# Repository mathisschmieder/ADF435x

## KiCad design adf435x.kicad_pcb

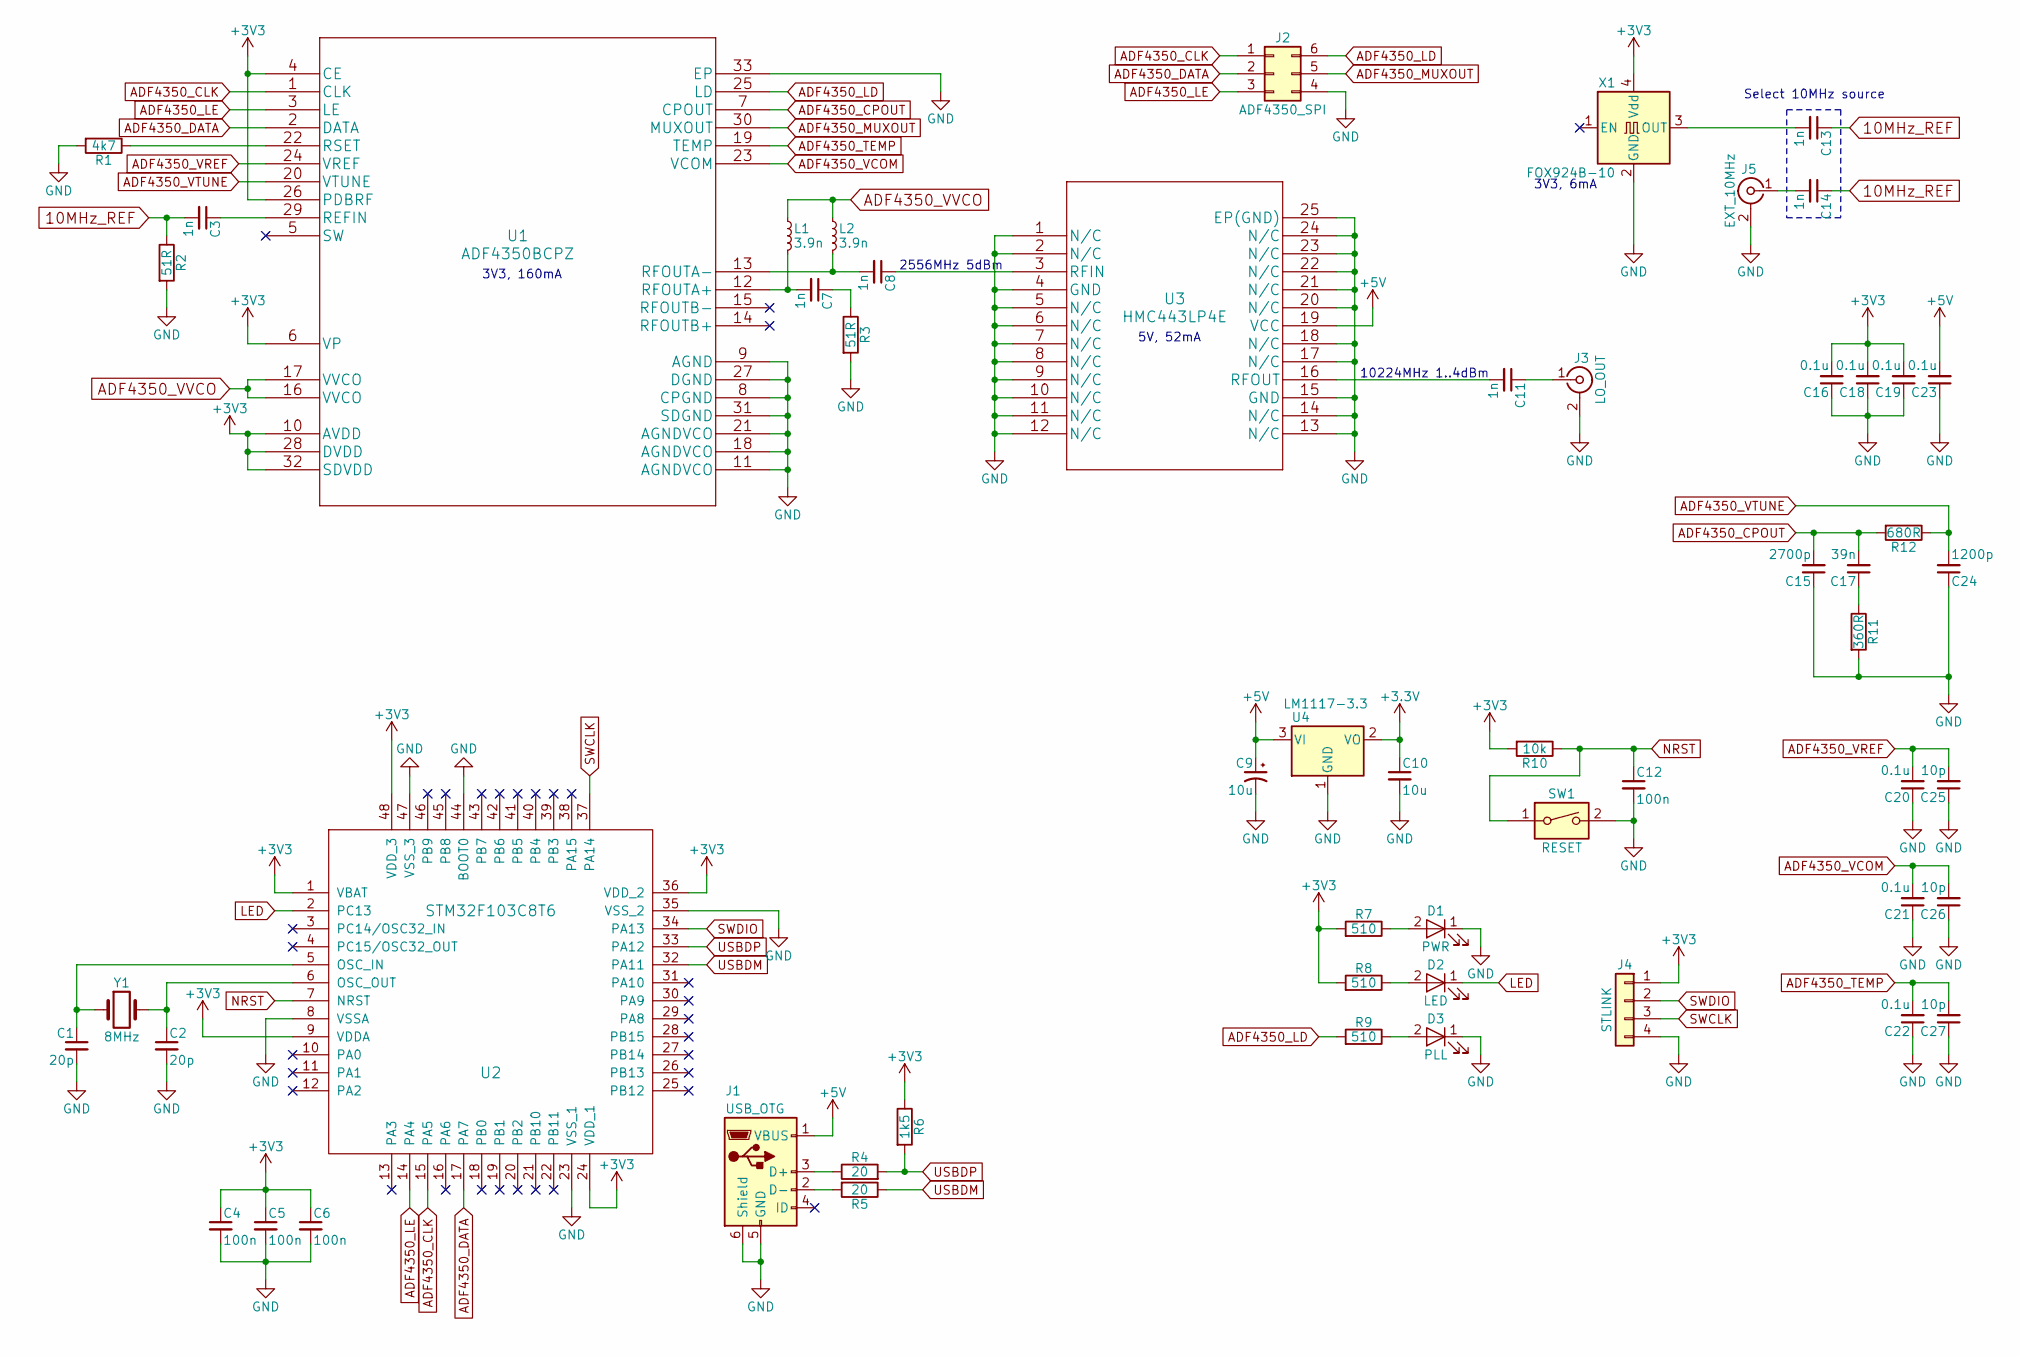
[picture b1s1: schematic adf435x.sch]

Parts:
C1, C2: 20p; C_0603
C3, C7, C8, C11, C13, C14: 1n; C_0603
C4, C5, C6, C12: 100n; C_0603
C9: 10u; CP_Tantalum_Case-A_EIA-3216-18_Reflow
C10: 10u; C_0603
C15: 2700p; C_0603
C16, C18, C19, C20, C21, C22, C23: 0.1u; C_0603
C17: 39n; C_0603
C24: 1200p; C_0603
C25, C26: 10p; C_0603
C27: 10p; LED_0603
D1: PWR; LED_0603
D2: LED; LED_0603
D3: PLL; LED_0603
J1: USB_OTG; USB_Micro-B_Wuerth-629105150521
J2: ADF4350_SPI; Pin_Header_Straight_2x03_Pitch1.27mm_SMD
J3: LO_OUT; Molex_SMA_Jack_Edge_Mount
J4: STLINK; Pin_Header_Straight_1x04_Pitch2.54mm
J5: EXT_10MHz; SMA_SMD_Jack_Straight
L1, L2: 3.9n; L_0603
R1: 4k7; R_0603
R2, R3: 51R; R_0603
R4, R5: 20; R_0603
R6: 1k5; R_0603
R7, R8, R9: 510; R_0603
R10: 10k; R_0603
R11: 360R; R_0603
R12: 680R; R_0603
SW1: RESET; SW_SPST_B3U-1000P
U1: ADF4350BCPZ; ADF4350BCPZ-RL
U2: STM32F103C8T6; LQFP-48_7x7mm_Pitch0.5mm
U3: HMC443LP4E
U4: LM1117-3.3; SOT-223-3_TabPin2
X1: FOX924B-10; Oscillator_SMD_Abracon_ASE-4pin_3.2x2.5mm
Y1: 8MHz; Crystal_SMD_Abracon_ABM3-2pin_5.0x3.2mm

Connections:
10MHz_REF: C3.2, C13.1, C14.1, R2.1
+5V: C9.1, C23.2, J1.1 (VBUS), U3.19 (VCC), U4.3 (VI)
ADF4350_CLK: J2.1, U1.1 (CLK), U2.15 (PA5)
ADF4350_CPOUT: C15.2, C17.2, R12.2, U1.7 (CPOUT)
ADF4350_DATA: J2.2, U1.2 (DATA), U2.17 (PA7)
ADF4350_LD: J2.6, R9.2, U1.25 (LD)
ADF4350_LE: J2.3, U1.3 (LE), U2.14 (PA4)
ADF4350_MUXOUT: J2.5, U1.30 (MUXOUT)
ADF4350_TEMP: C22.2, C27.2, U1.19 (TEMP)
ADF4350_VCOM: C21.2, C26.2, U1.23 (VCOM)
ADF4350_VREF: C20.2, C25.2, U1.24 (VREF)
ADF4350_VTUNE: C24.2, R12.1, U1.20 (VTUNE)
ADF4350_VVCO: L1.1, L2.1, U1.16 (VVCO), U1.17 (VVCO)
GND: C1.2, C2.2, C4.2, C5.2, C6.2, C9.2, C10.2, C12.2, C15.1, C16.1, C18.1, C19.1, C20.1, C21.1, C22.1, C23.1, C24.1, C25.1, C26.1, C27.1, D1.1 (K), D3.1 (K), J1.5 (GND), J1.6 (Shield), J2.4, J3.2 (Ext), J4.4, J5.2 (Ext), R1.2, R2.2, R3.2, R11.2, SW1.2, U1.8 (CPGND), U1.9 (AGND), U1.11 (AGNDVCO), U1.18 (AGNDVCO), U1.21 (AGNDVCO), U1.27 (DGND), U1.31 (SDGND), U1.33 (EP), U2.8 (VSSA), U2.23 (VSS_1), U2.35 (VSS_2), U2.44 (BOOT0), U2.47 (VSS_3), U3.1 (N/C), U3.2 (N/C), U3.4 (GND), U3.5 (N/C), U3.6 (N/C), U3.7 (N/C), U3.8 (N/C), U3.9 (N/C), U3.10 (N/C), U3.11 (N/C), U3.12 (N/C), U3.13 (N/C), U3.14 (N/C), U3.15 (GND), U3.17 (N/C), U3.18 (N/C), U3.20 (N/C), U3.21 (N/C), U3.22 (N/C), U3.23 (N/C), U3.24 (N/C), U3.25 (EP(GND)), U4.1 (GND), X1.2 (GND); also elsewhere on the board
LED: D2.1 (K), U2.2 (PC13)
NRST: C12.1, R10.1, SW1.1, U2.7 (NRST); also elsewhere on the board
unnamed: C1.1, U2.5 (OSC_IN), Y1.1
unnamed: C2.1, U2.6 (OSC_OUT), Y1.2
unnamed: C3.1, U1.29 (REFIN)
unnamed: C7.1, R3.1
unnamed: C7.2, L1.2, U1.12 (RFOUTA+)
unnamed: C8.1, U3.3 (RFIN)
unnamed: C8.2, L2.2, U1.13 (RFOUTA-)
unnamed: C11.1, J3.1 (In)
unnamed: C11.2, U3.16 (RFOUT)
unnamed: C13.2, X1.3 (OUT)
unnamed: C14.2, J5.1 (In)
unnamed: C17.1, R11.1
unnamed: D1.2 (A), R7.1
unnamed: D2.2 (A), R8.1
unnamed: D3.2 (A), R9.1
unnamed: J1.2 (D-), R5.2
unnamed: J1.3 (D+), R4.1
unnamed: R1.1, U1.22 (RSET)
SWCLK: J4.3, U2.37 (PA14)
SWDIO: J4.2, U2.34 (PA13)
USBDM: R5.1, U2.32 (PA11)
USBDP: R4.2, R6.2, U2.33 (PA12)

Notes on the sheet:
2556MHz 5dBm
10224MHz 1..4dBm
Select 10MHz source
5V, 52mA
3V3, 6mA
3V3, 160mA

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
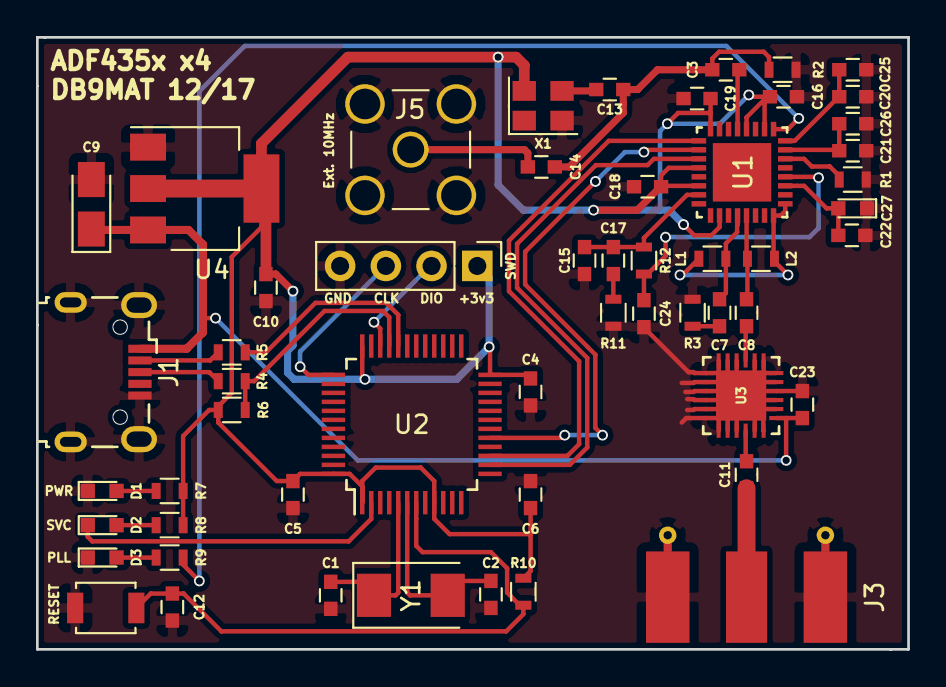
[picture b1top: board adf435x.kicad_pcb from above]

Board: 2 copper layers, 48.4 x 34.0 mm, 55 parts (0 on the bottom side), 38 nets.

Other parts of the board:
RESET: RESET; SW_SPST_B3U-1000P

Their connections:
GND: RESET.2; also elsewhere on the board
NRST: RESET.1; also elsewhere on the board

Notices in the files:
parts and their libraries:
Copyright 2016 Accelerated Designs. All rights reserved.
